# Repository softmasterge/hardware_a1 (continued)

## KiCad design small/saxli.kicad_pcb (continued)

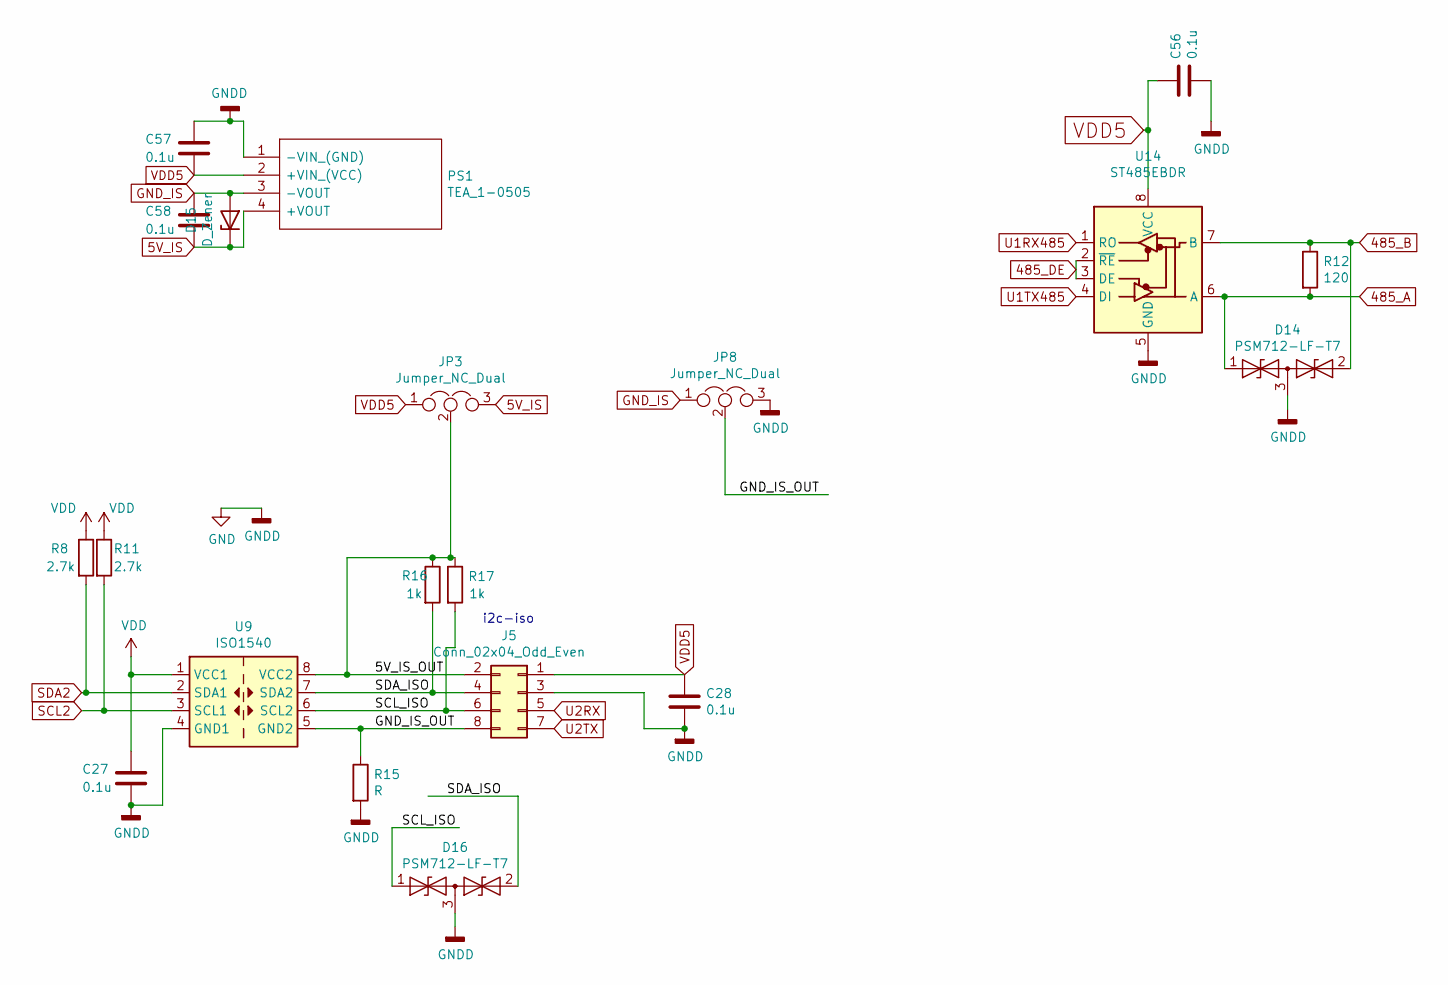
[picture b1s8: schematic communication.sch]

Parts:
C27, C28, C56, C57, C58: 0.1u; C_0603_1608Metric; Mpn 885012207098; LCSC C14663
D14, D16: PSM712-LF-T7; SOT-23; MPN PSM712-LF-T7; LCSC C32677
D15: D_Zener; D_MiniMELF; MPN ZMM5V6; LCSC C8062
J5: Conn_02x04_Odd_Even; PinHeader_2x04_P2.54mm_Vertical; Mpn Connector unknown; LCSC N/A
JP3, JP8: Jumper_NC_Dual; SolderJumper-3_P1.3mm_Open_Pad1.0x1.5mm; LCSC N/A
PS1: TEA_1-0505; TEA10505; Manufacturer_Part_Number TEA 1-0505; Mouser Part Number 495-TEA1-0505
R8, R11: 2.7k; R_0603_1608Metric; MPN 0603WAF2701T5E; LCSC C13167
R12: 120; R_0805_2012Metric; MPN 0805W8F1200T5E; LCSC C17437
R15: R; R_0805_2012Metric; MPN 0805W8F1001T5E; LCSC C17513
R16: 1k; R_0805_2012Metric; Mpn 0805W8F1001T5E; LCSC C17513
R17: 1k; R_0805_2012Metric; Mpn CRCW08051K00FKEAC; LCSC C17513
U9: ISO1540; SOIC-8_3.9x4.9mm_P1.27mm; MPN ISO1540DR; LCSC C179739
U14: ST485EBDR; SOIC-8_3.9x4.9mm_P1.27mm; MPN ST485EBDR; LCSC C81186

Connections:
5V_IS: C58.2, D15.1 (K), JP3.3, PS1.4 (+VOUT)
485_A: D14.1 (A1), R12.2, U14.6 (A); also elsewhere on the board
485_B: D14.2 (A2), R12.1, U14.7 (B); also elsewhere on the board
485_DE: U14.2 (~RE), U14.3 (DE); also elsewhere on the board
/communication/5V_IS_OUT: J5.2, JP3.2, R16.1, R17.1, U9.8 (VCC2)
/communication/GND_IS_OUT: J5.8, JP8.2, R15.1, U9.5 (GND2)
/communication/SCL_ISO: D16.1 (A1), J5.6, R17.2, U9.6 (SCL2)
/communication/SDA_ISO: D16.2 (A2), J5.4, R16.2, U9.7 (SDA2)
GND: C27.2, C28.2, C56.2, C57.1, D14.3 (common), D16.3 (common), J5.3, JP8.3, PS1.1 (-VIN_(GND)), R15.2, U9.4 (GND1), U14.5 (GND); also elsewhere on the board
GND_IS: C58.1, D15.2 (A), JP8.1, PS1.3 (-VOUT)
SCL2: R11.2, U9.3 (SCL1); also elsewhere on the board
SDA2: R8.2, U9.2 (SDA1); also elsewhere on the board
U1RX485: U14.1 (RO); also elsewhere on the board
U1TX485: U14.4 (DI); also elsewhere on the board
U2RX: J5.5; also elsewhere on the board
U2TX: J5.7; also elsewhere on the board
VDD3: C27.1, R8.1, R11.1, U9.1 (VCC1); also elsewhere on the board
VDD5: C28.1, C56.1, C57.2, J5.1, JP3.1, PS1.2 (+VIN_(VCC)), U14.8 (VCC); also elsewhere on the board

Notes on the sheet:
i2c-iso

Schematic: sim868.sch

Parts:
C38: 22u; R_0805_2012Metric; MPN CL21A226MAQNNNE; LCSC C45783
C43: 100n; C_0603_1608Metric; MPN CC0603KRX7R9BB104; LCSC C14663
C45: 47p; C_0603_1608Metric; MPN CL10C470JB8NNNC; LCSC C1671
C46, C51: 100u; CP_EIA-3528-21_Kemet-B; MPN TAJB107K006RNJ; LCSC C16133
D11: D_Zener; D_MiniMELF; MPN ZMM5V6; LCSC C8062
D12: LED; LED_0805_2012Metric_Pad1.15x1.40mm_HandSolder; MPN 17-21SUYC/TR8; LCSC C2296
D13: LED; LED_0805_2012Metric_Pad1.15x1.40mm_HandSolder; MPN FC-2012HRK-620D; LCSC C84256
IC2: SIM808; MPN SIM808; LCSC N/A
J1: 78800-0001; 788000001; Mouser Part Number 538-78800-0001
J10: Conn_01x06_Female; PinHeader_1x06_P2.54mm_Vertical; LCSC N/A
J11, J12: Conn_Coaxial; SMA_Amphenol_901-144_Vertical; MPN 73391-0070; LCSC N/A
JP1, JP2: Jumper; SolderJumper-2_P1.3mm_Open_RoundedPad1.0x1.5mm; LCSC N/A
L3: INDUCTOR; L_0603_1608Metric; MPN SDCL1608C27NJTDF; LCSC C12100
Q1, Q2, Q3: 2N7002; SOT-23; MPN 2N7002; LCSC C8545
R40, R42, R47, R48, R49: 5.1k; R_0603_1608Metric; MPN 0603WAF5101T5E; LCSC C23186
R41, R46: 1k; R_0603_1608Metric; MPN 0603WAF1001T5E; LCSC C21190
R43, R44, R45: 22; R_0603_1608Metric; MPN 0603WAF220JT5E; LCSC C23345
R50, R51: 200; R_0603_1608Metric; MPN 0603WAF2000T5E; LCSC C8218
R55: R; R_0603_1608Metric; MPN 0603WAF5100T5E; LCSC C23193
U16: SRV05-4; SOT-23-6; MPN SRV05-4-P-T7; LCSC C85364

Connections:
/sim868/NETLIGHT: IC2.50 (NETLIGHT), Q2.1 (G), R48.2
/sim868/RST: IC2.8 (PWRKEY), J10.3, Q1.3 (D)
/sim868/SIM_CLK: J1.C3, R44.1, U16.3 (IO2)
/sim868/SIM_IO: J1.C7, R45.1, U16.4 (IO3)
/sim868/SIM_RST: J1.C2, R43.1, U16.1 (IO1)
/sim868/SIM_RX: J10.4, JP2.1, R41.1, R42.2
/sim868/SIM_TX: J10.5, JP1.1, R46.1
/sim868/SIM_VDD: IC2.29 (SIM_VDD), J1.C1, U16.5 (VP); also elsewhere on the board
/sim868/STATUS: IC2.49 (STATUS), Q3.1 (G), R49.2
/sim868/VDD_EXT: IC2.7 (VDD_EXT), R47.2, R55.1
GND: C38.2, C43.2, C45.2, C46.2, C51.2, D11.2 (A), IC2.1 (GND_1), IC2.2 (GND_2), IC2.3 (GND_3), IC2.18 (GND_4), IC2.19 (MIC1P), IC2.20 (MIC1N), IC2.23 (ADC0), IC2.24 (ADC1), IC2.28 (GND_5), IC2.34 (GND_6), IC2.36 (GND_7), IC2.40 (GND_8), IC2.51 (GND_9), IC2.52 (GND_10), IC2.54 (GND_11), IC2.64 (GND_12), IC2.65 (GND_13), IC2.67 (GND_14), IC2.68 (GND_15), J1.C5, J1.MP1, J1.MP2, J10.6, J11.2 (Ext), J12.2 (Ext), Q1.2 (S), Q2.2 (S), Q3.2 (S), R40.1, R42.1, R48.1, R49.1, U16.2 (VN); also elsewhere on the board
GPS_ANT: IC2.35 (GPS_ANT), J11.1 (In), L3.2
GSM_ANT: IC2.66 (GSM_ANT), J12.1 (In)
unnamed: D12.1 (K), R50.1
unnamed: D13.1 (K), R51.1
unnamed: IC2.14 (TXD), JP1.2
unnamed: IC2.15 (RXD), JP2.2
unnamed: IC2.30 (SIM_DATA), R45.2
unnamed: IC2.31 (SIM_CLK), R44.2
unnamed: IC2.32 (SIM_RST), R43.2
unnamed: IC2.33 (SIM_DET), R47.1
unnamed: L3.1, R55.2
unnamed: Q2.3 (D), R50.2
unnamed: Q3.3 (D), R51.2
POWER_SIM: C38.1, C43.1, C45.1, C46.1, C51.1, D11.1 (K), D12.2 (A), D13.2 (A), IC2.4 (VBAT_1), IC2.5 (VBAT_2), IC2.6 (VBAT_3), J10.2; also elsewhere on the board
SIM800_RST: Q1.1 (G), R40.2; also elsewhere on the board
U3RXSIM800: R46.2; also elsewhere on the board
U3TXSIM800: R41.2; also elsewhere on the board
USB_DM: IC2.27 (USB_DN)
USB_DP: IC2.26 (USB_DP)
USB_VBUS: IC2.25 (VCHG)

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
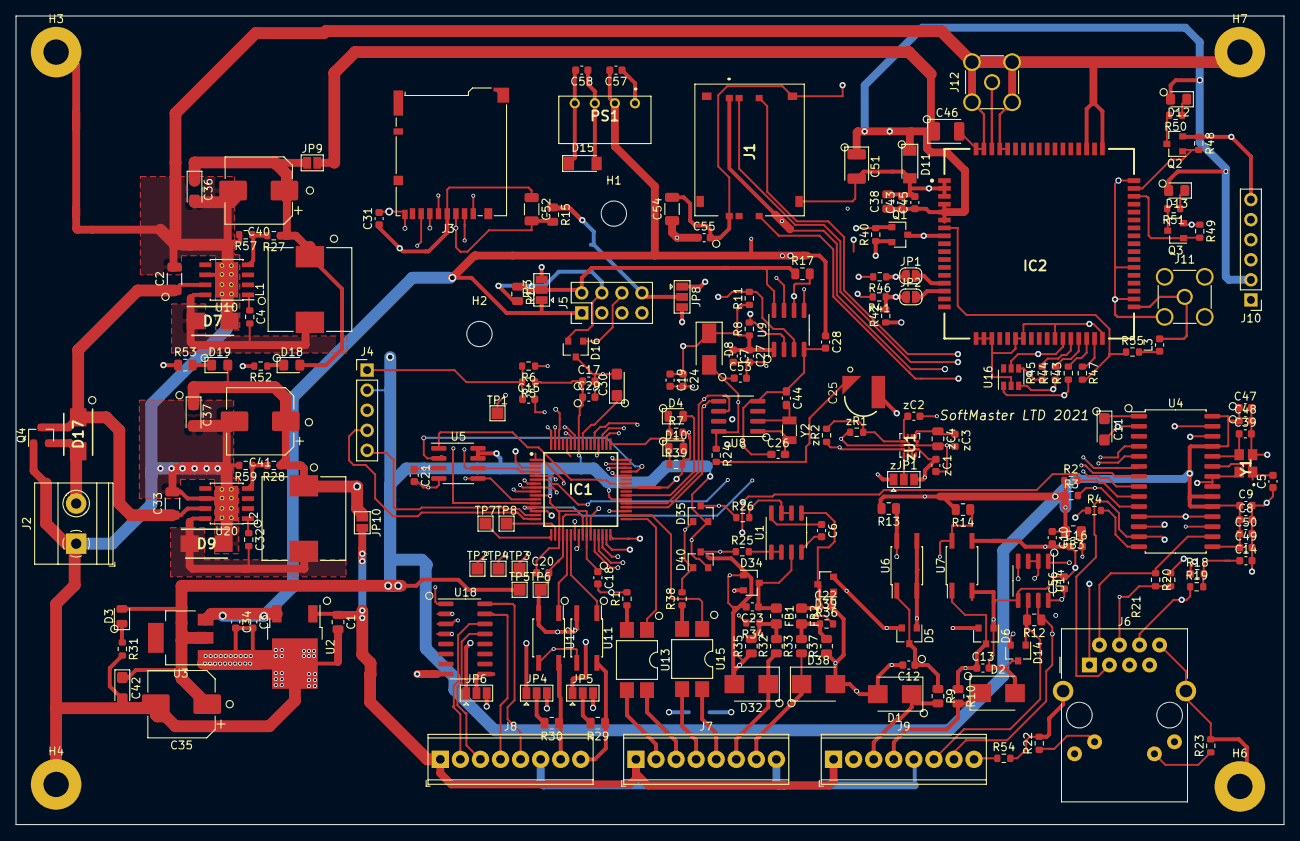
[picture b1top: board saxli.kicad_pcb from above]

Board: 4 copper layers, 160.5 x 102.4 mm, 217 parts (1 on the bottom side), 153 nets.

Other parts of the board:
C52, C54: 10uF; C_1206_3216Metric
C53, C55: 0.1u; C_0603_1608Metric
JP9, JP10: Jumper; SolderJumper-2_P1.3mm_Open_Pad1.0x1.5mm
zC1: 10n; C_0603_1608Metric
zC2, zC3: 0.1u; C_0603_1608Metric
zC4: C; C_0805_2012Metric
zJP1: Jumper_NC_Dual; SolderJumper-3_P1.3mm_Open_Pad1.0x1.5mm
zR1, zR2: 5.1k; R_0603_1608Metric
zU1: ICM-20600; ICM20600

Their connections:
/sim868/SIM_VDD: C54.1, C55.1; also elsewhere on the board
GND: C52.2, C53.2, C54.2, C55.2, zC1.2, zC2.2, zC3.2, zC4.2, zJP1.1, zU1.6, zU1.7; also elsewhere on the board
unnamed 72: JP9.1; also elsewhere on the board
unnamed 75: C53.1; also elsewhere on the board
unnamed: zC2.1, zU1.11
unnamed: zC3.1, zC4.1, zU1.8
unnamed: zJP1.2, zU1.1
POWER_SIM: JP9.2; also elsewhere on the board
SCL1: zR1.1, zU1.13; also elsewhere on the board
SDA1: zR2.1, zU1.14; also elsewhere on the board
VDD3: C52.1, zC1.1, zJP1.3, zR1.2, zR2.2, zU1.5, zU1.12; also elsewhere on the board

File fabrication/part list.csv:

Comment,Designator,Footprint,LCSC Part #
1u Unpolarized capacitor,C1,R_0805_2012Metric, C28323
10uF Unpolarized capacitor,"C2,C33,C52,C54",C_1206_3216Metric,C13585
0.1u Unpolarized capacitor,"C3,C6,C7,C8,C9,C10,C15,C16,C17,C18,C19,C20,C21,C24,C27,C28,C29,C31,C34,C53,C55,C56,C57,C58",C_0603_1608Metric,C14663
10n Unpolarized capacitor,"C4,C32",R_0603_1608Metric, C57112
12pF Unpolarized capacitor,"C5,C39",C_0603_1608Metric,C38523
10u Polarized capacitor,"C11,C30,C36,C37,C42",CP_EIA-3216-18_Kemet-A,C7171
1n Unpolarized capacitor,"C12,C13,C22,C23",C_0603_1608Metric,C46653
10n Unpolarized capacitor,C14,C_0603_1608Metric, C57112
XH414HG-IV01E ,C25,CAP_XH414HG-IV01E,C38065
20pf Unpolarized capacitor,"C26,C44",C_0603_1608Metric_Pad1.08x0.95mm_HandSolder,C1648
220u Polarized capacitor,"C35,C40,C41",CP_Elec_8x10, C311611
22u Unpolarized capacitor,C38,R_0805_2012Metric, C45783
100n Unpolarized capacitor,C43,C_0603_1608Metric,C14663
47p Unpolarized capacitor,C45,C_0603_1608Metric, C1671
100u Unpolarized capacitor,"C46,C51",CP_EIA-3528-21_Kemet-B, C16133
1u Unpolarized capacitor,"C47,C49",C_0603_1608Metric,C15849
10u Unpolarized capacitor,"C48,C50",C_0603_1608Metric,C344022
"P6SMB30CA 1500W unidirectional TRANSZORB® Transient Voltage Suppressor, DO-201AE","D1,D2,D32,D38",D_SMB,C320521
LED Light emitting diode,"D3,D4,D10",LED_0805_2012Metric,C84256
BAT54S schottky barrier diode,"D5,D6,D34,D35,D39,D40",SOT-23,C122856
SS34B-HF ,"D7,D9,D17",DIOM5336X320N,C8678
"SS14 Diode, anode on pin 1, for simulation only!",D8,D_SMA, C2480
D_Zener Zener diode,"D11,D15",D_MiniMELF,C8062
LED Light emitting diode,"D12,D13,D18,D19",LED_0805_2012Metric_Pad1.15x1.40mm_HandSolder,C205449
"PSM712-LF-T7 7V/12V, 600W Asymmetrical TVS Diode Array, SOT-23","D14,D16",SOT-23,C32677
Ferrite_Bead Ferrite bead,"FB1,FB2,FB3",R_0805_2012Metric_Pad1.20x1.40mm_HandSolder,C1017
MountingHole Mounting Hole without connection,"H1,H2",MountingHole_3.2mm_M3,N/A
MountingHole_Pad Mounting Hole with connection,"H3,H4,H6,H7",MountingHole_3.2mm_M3_Pad,N/A
PIC32MX350F256H-V_PT ,IC1,QFP50P1200X1200X120-64N,N/A
SIM808 GSM GPRS CELLULAR MODULE,IC2,SIM808,N/A
78800-0001 Molex 78800 Series Vertical Hinged Micro SIM Card Connector with SMT Termination,J1,788000001,N/A
"Screw_Terminal_01x02 Generic screw terminal, single row, 01x02, script generated (kicad-library-utils/schlib/autogen/connector/)",J2,"TerminalBlock_Phoenix_MKDS-1,5-2-5.08_1x02_P5.08mm_Horizontal",N/A
Micro_SD_Card Micro SD Card Socket,J3,microSD_HC_Hirose_DM3BT-DSF-PEJS,N/A
"Conn_01x05_Female Generic connector, single row, 01x05, script generated (kicad-library-utils/schlib/autogen/connector/)",J4,PinHeader_1x05_P2.54mm_Vertical,N/A
"Conn_02x04_Odd_Even Generic connector, double row, 02x04, odd/even pin numbering scheme (row 1 odd numbers, row 2 even numbers), script generated (kicad-library-utils/schlib/autogen/connector/)",J5,PinHeader_2x04_P2.54mm_Vertical,N/A
"RJ45_Amphenol_RJMG1BD3B8K1ANR 1 Port RJ45 Magjack Connector Through Hole 10/100 Base-T, AutoMDIX",J6,RJ45_Amphenol_RJMG1BD3B8K1ANR,N/A
"Screw_Terminal_01x08 Generic screw terminal, single row, 01x08, script generated (kicad-library-utils/schlib/autogen/connector/)","J7,J8,J9","TerminalBlock_Phoenix_MPT-0,5-8-2.54_1x08_P2.54mm_Horizontal",N/A
"Conn_01x06_Female Generic connector, single row, 01x06, script generated (kicad-library-utils/schlib/autogen/connector/)",J10,PinHeader_1x06_P2.54mm_Vertical,N/A
"Conn_Coaxial coaxial connector (BNC, SMA, SMB, SMC, Cinch/RCA, ...)","J11,J12",SMA_Amphenol_901-144_Vertical,N/A
"Jumper Jumper, normally closed","JP1,JP2",SolderJumper-2_P1.3mm_Open_RoundedPad1.0x1.5mm,N/A
"Jumper_NC_Dual Dual jumper, normally closed","JP3,JP4,JP5,JP6,JP7,JP8",SolderJumper-3_P1.3mm_Open_Pad1.0x1.5mm,N/A
22u Inductor symbol for simulation only,"L1,L2",L_10.4x10.4_H4.8, C182173
INDUCTOR Inductor symbol for simulation only,L3,L_0603_1608Metric,C12100
TEA_1-0505 Isolated DC/DC Converters 1W 4.5-5.5Vin 5Vout 200mA unreg SIP-4,PS1,TEA10505,N/A
"2N7002 0.115A Id, 60V Vds, N-Channel MOSFET, SOT-23","Q1,Q2,Q3",SOT-23,C8545
"AO3401A -4.0A Id, -30V Vds, P-Channel MOSFET, SOT-23",Q4,SOT-23,C15127
330 Resistor,"R1,R38",R_0603_1608Metric,C23138
10k Resistor,"R2,R3,R5,R27,R28,R54",R_0603_1608Metric,C25804
2.32k 1% Resistor,R4,R_0603_1608Metric,C22905
1k Resistor,"R6,R25,R26,R41,R46",R_0603_1608Metric,C21190
100 Resistor,"R7,R22,R23,R24,R31,R39",R_0603_1608Metric,C22775
2.7k Resistor,"R8,R11",R_0603_1608Metric,C13167
2.2k Resistor,"R9,R10",R_0805_2012Metric,C17520
120 Resistor,R12,R_0805_2012Metric,C17437
1k Resistor,"R13,R14,R16,R17,R29,R30,R53",R_0805_2012Metric,C17513
R Resistor,R15,R_0805_2012Metric,C17513
49.9 %1 Resistor,"R18,R19,R20,R21",R_0603_1608Metric,C23185
3.6k Resistor,"R32,R33",R_0805_2012Metric,C18359
na Resistor,"R34,R36",R_0603_1608Metric,N/A
560 Resistor,"R35,R37",R_0805_2012Metric,C28636
5.1k Resistor,"R40,R42,R47,R48,R49",R_0603_1608Metric,C23186
22 Resistor,"R43,R44,R45",R_0603_1608Metric,C23345
200 Resistor,"R50,R51,R52",R_0603_1608Metric,C8218
R Resistor,R55,R_0603_1608Metric,C23193
4.3k Resistor,R57,R_0603_1608Metric,C23159
1.1k Resistor,R59,R_0603_1608Metric,C22764
TestPoint test point,"TP1,TP2,TP3,TP4,TP5,TP6,TP7,TP8",TestPoint_Pad_1.5x1.5mm,N/A
"LM358 Low-Power, Dual Operational Amplifiers, DIP-8/SOIC-8/TO-99-8",U1,SOIC-8_3.9x4.9mm_P1.27mm,C7950
"LM7805_TO220 Positive 1A 35V Linear Regulator, Fixed Output 5V, TO-220",U2,TO-252-2,C54285
"AMS1117-3.3 800mA Fixed Low Drop Positive Voltage Regulator, Fixed Output 3.3V, SOT-223",U3,SOT-223,C6186
"ENC28J60x-SS ENC28J60 Single Chip Ethernet Interface, SSOP-28",U4,SOIC-28W_7.5x17.9mm_P1.27mm, C47351
"AT25M02 Microchip SPI Serial EEPROM, DIP-8/SOIC-8/TSSOP-8",U5,SOIC-8_3.9x4.9mm_P1.27mm,N/A
"EL357N(C)(TA)-G DC Optocoupler, Vce 35V, CTR 50-300%, DIP-4","U6,U7,U11,U12",SO-4_4.4x3.6mm_P2.54mm,C29981
"PCF8563T Realtime Clock/Calendar I2C Interface, SOIC-8",U8,SOIC-8_3.9x4.9mm_P1.27mm,C7440
"ISO1540 I2C Isolator, 2.5 kVrms, Bidirectional clock and data, SOIC-8",U9,SOIC-8_3.9x4.9mm_P1.27mm, C179739
"TPS5430DDAR 3A, Step Down Swift Converter, Adjustable Output Voltage, 5.5-36V Input Voltage, PowerSO-8","U10,U20",TI_SO-PowerPAD-8_ThermalVias,C9864
"ASSR-1218 Form A, Solid State Relay (Photo MOSFET) 60V, 0.2A, 10Ohm, SO-4","U13,U15",SMDIP-4_W7.62mm,C129282
"ST485EBDR Half duplex RS-485/RS-422, 5 Mbps, ±15kV electro-static discharge (ESD) protection, no slew-rate, with low-power shutdown, with receiver/driver enable, 256 transceiver on the bus - 40 to 85 °C, SOIC-8",U14,SOIC-8_3.9x4.9mm_P1.27mm,C81186
"SRV05-4 ESD Protection Diodes with Low Clamping Voltage, SOT-23-6",U16,SOT-23-6,C85364
"ULN2003A High Voltage, High Current Darlington Transistor Arrays, SOIC16/SOIC16W/DIP16/TSSOP16",U18,SOIC-16W_5.3x10.2mm_P1.27mm,C7512
YSX321SL Crystal,Y1,YSX321SL,C9006
Crystal Two pin crystal,Y2,Crystal_SMD_3215-2Pin_3.2x1.5mm,C32346
10n Unpolarized capacitor,zC1,C_0603_1608Metric,C57112
0.1u Unpolarized capacitor,"zC2,zC3",C_0603_1608Metric,C14663
C Unpolarized capacitor,zC4,C_0805_2012Metric,C49217
"Jumper_NC_Dual Dual jumper, normally closed",zJP1,SolderJumper-3_P1.3mm_Open_Pad1.0x1.5mm,N/A
5.1k Resistor,"zR1,zR2",R_0603_1608Metric,C23186
"ICM-20600 IMUs - Inertial Measurement Units Low-Power, High-Performance Integrated 6-Axis MEMS MotionTracking  Device in 2.5mm x 3mm Package",zU1,ICM20600,C124140

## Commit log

2021-02-10 sim800 changed to sim808
2021-02-10 simcard colder changed to 78800-0001
2021-02-11 All routed PGEC1 grounded according to errata
2021-02-11 connector rotated.
    added rs485 output.
    TODO: add bluetooth port.
    check all parts
    preaper bom list
    prepare mouser list
2021-02-12 GPS connector moved,
    antenna matching networks removed
    SUPERCAPACITOR from jlpcb used.
2021-02-12 minor updates
2021-02-15 BOM updated
    Layout changed
2021-02-16 Battery Footprint changed.
    Few mods
2021-02-16 minor changes
2021-02-16 ENC28j60 package changed to soic 28 17.9
    TODO: route
2021-02-16 ENC28j60 routed
2021-02-16 ENC28j60 rerouted
2021-02-17 SPI change:
    ENC28j60 on one spi
    SDCARD and EEPROM on the other.
2021-02-17 Ethernet connector connection fix
2021-02-17 sdcard and clock capacitor added.
2021-02-17 minor changed
2021-02-17 3.3V changed to basic part.
    thermal vias added for 5V regulator
2021-02-17 capacitor added to sd card
2021-02-17 power supply ldo changes
2021-02-18 Isolated DCDC added
    power LED added
    reverse voltage protection added
2021-02-18 fabrication output prepared
2021-02-18 working on JLCPCB orientations
2021-02-19 JLCPCB orientation fixed
2021-02-23 oscillator footprint and capacitors changed
2021-02-24 JLCPCB crystal capacitor part number change
2021-02-25 iso voltage update
    minor changes
2021-02-25 25 MHZ crystal part added.
2021-02-25 lm358 pn change in the output file
2021-02-26 accelerometer added
2021-03-10 ULN2003 footprint updated
